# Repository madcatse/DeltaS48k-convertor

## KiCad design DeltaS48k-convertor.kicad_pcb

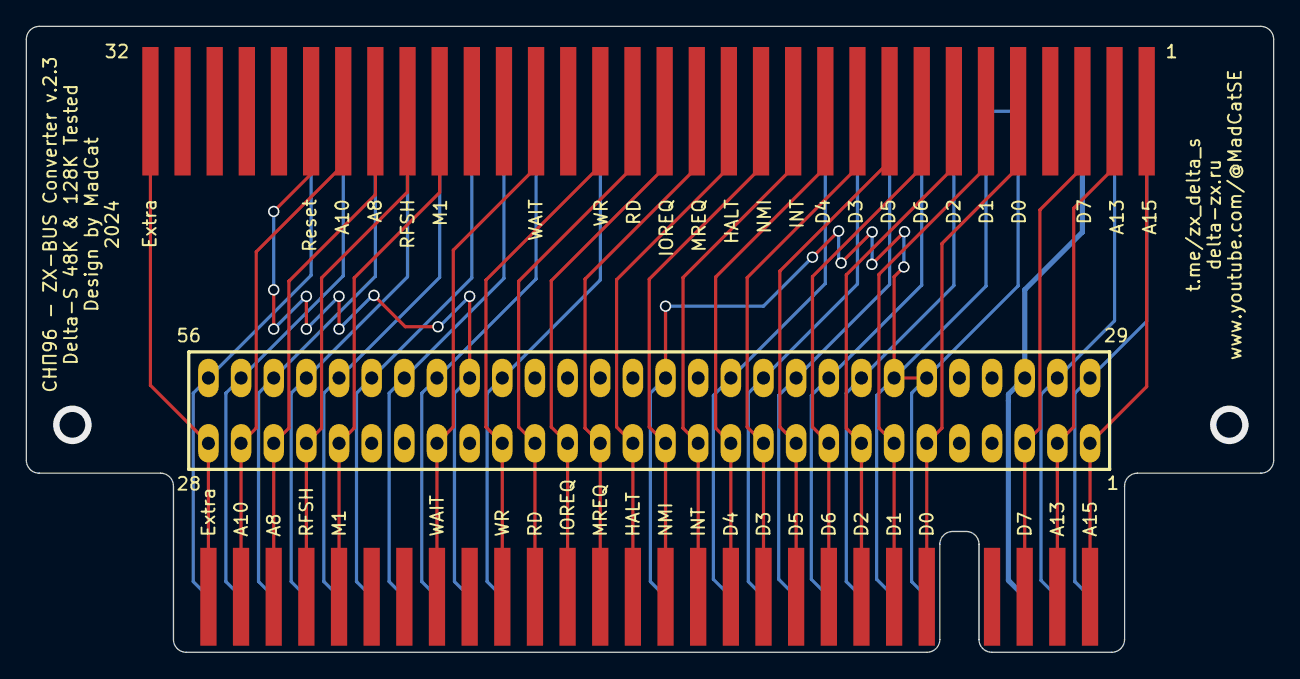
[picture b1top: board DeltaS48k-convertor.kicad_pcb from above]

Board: 2 copper layers, 97.0 x 48.7 mm, 3 parts (0 on the bottom side), 42 nets.

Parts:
J1: SNP; SNP96
J2: ZX1; ZX SPECTRUM EDGE CONNECTOR (HORIZONTAL)
SLOT: ZX1; Spectrum_edge_slot_FIXED

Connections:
A0: J1.40 (A0), J2.37 (A0), SLOT.37 (A0)
A1: J1.41 (A1), J2.38 (A1), SLOT.38 (A1)
A2: J1.42 (A2), J2.39 (A2), SLOT.39 (A2)
A3: J1.43 (A3), J2.40 (A3), SLOT.40 (A3)
A4: J1.55 (A4), J2.52 (A4), SLOT.52 (A4)
A5: J1.54 (A5), J2.51 (A5), SLOT.51 (A5)
A6: J1.53 (A6), J2.50 (A6), SLOT.50 (A6)
A7: J1.52 (A7), J2.49 (A7), SLOT.49 (A7)
A8: J1.25 (A8), J2.26 (A8), SLOT.26 (A8)
A9: J1.58 (A9), J2.55 (A9), SLOT.55 (A9)
A10: J1.26 (A10), J2.27 (A10), SLOT.27 (A10)
A11: J1.59 (A11), J2.56 (A11), SLOT.56 (A11)
A12: J1.34 (A12), J2.30 (A12), SLOT.30 (A12)
A13: J1.2 (A13), J2.2 (A13), SLOT.2 (A13)
A14: J1.33 (A14), J2.29 (A14), SLOT.29 (A14)
A15: J1.1 (A15), J2.1 (A15), SLOT.1 (A15)
BUSACK: J1.57 (ПЗШ), J2.54 (BUSACK), SLOT.54 (BUSACK)
BUSRQ: J1.50 (ЗАПРШ), J2.47 (BUSRQ), SLOT.47 (BUSRQ)
CLK: J1.39, J2.36 (CLK), SLOT.36 (CLK)
D0: J1.5 (D0), J2.6 (D0), SLOT.6 (D0)
D1: J1.6 (D1), J2.7 (D1), SLOT.7 (D1)
D2: J1.7 (D2), J2.8 (D2), SLOT.8 (D2)
D3: J1.10 (D3), J2.11 (D3), SLOT.11 (D3)
D4: J1.11 (D4), J2.12 (D4), SLOT.12 (D4)
D5: J1.9 (D5), J2.10 (D5), SLOT.10 (D5)
D6: J1.8 (D6), J2.9 (D6), SLOT.9 (D6)
D7: J1.3 (D7), J2.3 (D7), SLOT.3 (D7)
EXTRA: J1.32 (BD7), J2.28 (NC), SLOT.28 (NC)
GND: J1.37 (Общий), J1.38 (Общий), J2.34 (GND), J2.35 (GND), J2.42 (GND), SLOT.34 (GND), SLOT.35 (GND), SLOT.42 (GND)
HALT: J1.14 (СТОП), J2.15 (HALT), SLOT.15 (HALT)
INT: J1.12 (ПР), J2.13 (INT), SLOT.13 (INT)
IOREQ: J1.16 (ВУ), J2.17 (IORQ), SLOT.17 (IORQ)
M1: J1.23 (М1), J2.24 (M1), SLOT.24 (M1)
MREQ: J1.15 (ОЗУ), J2.16 (MREQ), SLOT.16 (MREQ)
NMI: J1.13 (НПР), J2.14 (NMI), SLOT.14 (NMI)
RD: J1.17 (ЧТ), J2.18 (RD), SLOT.18 (RD)
RESET: J1.27 (СБРОС), J2.48 (RESET), SLOT.48 (RESET)
RFSH: J1.24 (РГН), J2.25 (RFSH), SLOT.25 (RFSH)
ROMCS: J1.56 (БЛК_ПЗУ), J2.53 (ROMCS), SLOT.53 (ROMCS)
VCC: J1.35 ("+5"), J2.31 (+5V), SLOT.31 (+5V)
WAIT: J1.20 (ОЖИД), J2.21 (WAIT), SLOT.21 (WAIT)
WR: J1.18 (ЗП), J2.19 (WR), SLOT.19 (WR)

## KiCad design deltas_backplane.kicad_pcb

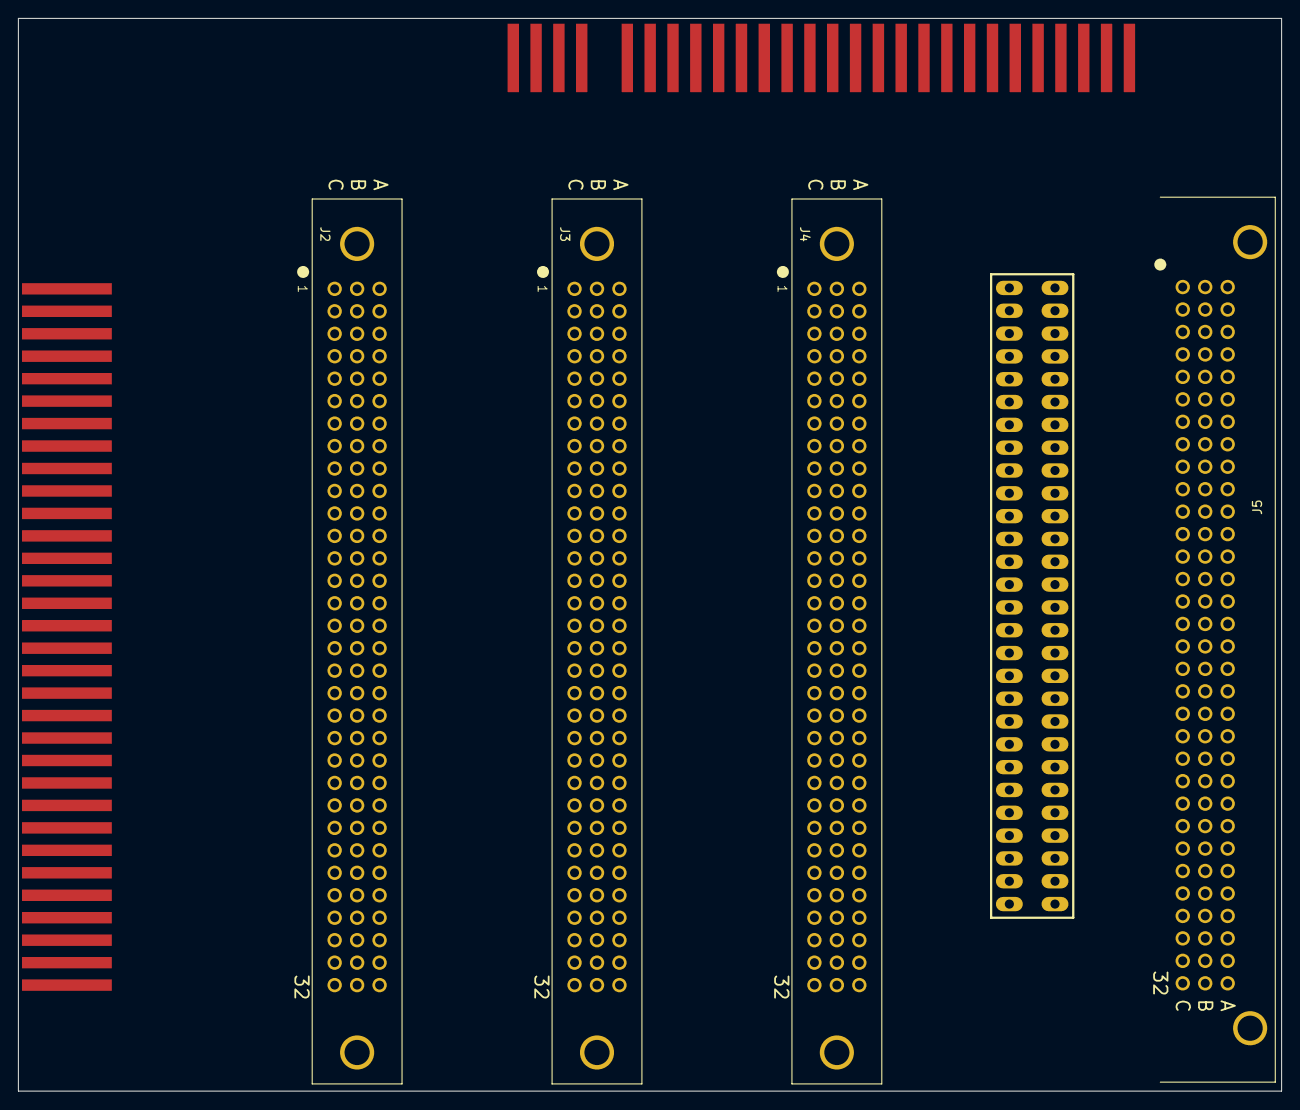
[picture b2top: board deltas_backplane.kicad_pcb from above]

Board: 2 copper layers, 140.6 x 119.4 mm, 7 parts (0 on the bottom side), 55 nets, no tracks yet.

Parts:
J1: SNP_female_straight; snp_straight
J2, J3, J4: SNP_female_straight; snp59_96_male_straight
J5: SNP_male_angle; snp59_96_female_angle_3
J6: zx_bus; ZX SPECTRUM EDGE CONNECTOR (HORIZONTAL)
J7: zx_bus; Spectrum_edge_slot_FIXED

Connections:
+5V: J1.35 ("+5"), J2.35 ("+5"), J3.35 ("+5"), J4.35 ("+5"), J5.35 ("+5"), J6.31 (+5V), J7.31 (+5V)
A0: J1.40 (A0), J2.40 (A0), J3.40 (A0), J4.40 (A0), J5.40 (A0), J6.37 (A0), J7.37 (A0)
A1: J1.41 (A1), J2.41 (A1), J3.41 (A1), J4.41 (A1), J5.41 (A1), J6.38 (A1), J7.38 (A1)
A2: J1.42 (A2), J2.42 (A2), J3.42 (A2), J4.42 (A2), J5.42 (A2), J6.39 (A2), J7.39 (A2)
A3: J1.43 (A3), J2.43 (A3), J3.43 (A3), J4.43 (A3), J5.43 (A3), J6.40 (A3), J7.40 (A3)
A4: J1.55 (A4), J2.55 (A4), J3.55 (A4), J4.55 (A4), J5.55 (A4), J6.52 (A4), J7.52 (A4)
A5: J1.54 (A5), J2.54 (A5), J3.54 (A5), J4.54 (A5), J5.54 (A5), J6.51 (A5), J7.51 (A5)
A6: J1.53 (A6), J2.53 (A6), J3.53 (A6), J4.53 (A6), J5.53 (A6), J6.50 (A6), J7.50 (A6)
A7: J1.52 (A7), J2.52 (A7), J3.52 (A7), J4.52 (A7), J5.52 (A7), J6.49 (A7), J7.49 (A7)
A8: J1.25 (A8), J2.25 (A8), J3.25 (A8), J4.25 (A8), J5.25 (A8), J6.26 (A8), J7.26 (A8)
A9: J1.58 (A9), J2.58 (A9), J3.58 (A9), J4.58 (A9), J5.58 (A9), J6.55 (A9), J7.55 (A9)
A10: J1.26 (A10), J2.26 (A10), J3.26 (A10), J4.26 (A10), J5.26 (A10), J6.27 (A10), J7.27 (A10)
A11: J1.59 (A11), J2.59 (A11), J3.59 (A11), J4.59 (A11), J5.59 (A11), J6.56 (A11), J7.56 (A11)
A12: J1.34 (A12), J2.34 (A12), J3.34 (A12), J4.34 (A12), J5.34 (A12), J6.30 (A12), J7.30 (A12)
A13: J1.2 (A13), J2.2 (A13), J3.2 (A13), J4.2 (A13), J5.2 (A13), J6.2 (A13), J7.2 (A13)
A14: J1.33 (A14), J2.33 (A14), J3.33 (A14), J4.33 (A14), J5.33 (A14), J6.29 (A14), J7.29 (A14)
A15: J1.1 (A15), J2.1 (A15), J3.1 (A15), J4.1 (A15), J5.1 (A15), J6.1 (A15), J7.1 (A15)
A19_SNP: J1.51 (BD1), J2.51 (BD1), J3.51 (BD1), J4.51 (BD1), J5.51 (BD1)
A28_SNP: J1.60 (P5), J2.60 (P5), J3.60 (P5), J4.60 (P5), J5.60 (P5)
A29_SNP: J1.61 (BD3), J2.61 (BD3), J3.61 (BD3), J4.61 (BD3), J5.61 (BD3)
A30_SNP: J1.62 (BD5), J2.62 (BD5), J3.62 (BD5), J4.62 (BD5), J5.62 (BD5)
A31_SNP: J1.63 (BD6), J2.63 (BD6), J3.63 (BD6), J4.63 (BD6), J5.63 (BD6)
B19_SNP: J1.19 (BD2), J2.19 (BD2), J3.19 (BD2), J4.19 (BD2), J5.19 (BD2)
B21_SNP: J1.21 (P1), J2.21 (P1), J3.21 (P1), J4.21 (P1), J5.21 (P1)
B22_SNP: J1.22 (P2), J2.22 (P2), J3.22 (P2), J4.22 (P2), J5.22 (P2)
B28_SNP: J1.28 (P4), J2.28 (P4), J3.28 (P4), J4.28 (P4), J5.28 (P4)
B29_SNP: J1.29 (P5), J2.29 (P5), J3.29 (P5), J4.29 (P5), J5.29 (P5)
B30_SNP: J1.30 (BD4), J2.30 (BD4), J3.30 (BD4), J4.30 (BD4), J5.30 (BD4)
B31_SNP: J1.31 (BD0), J2.31 (BD0), J3.31 (BD0), J4.31 (BD0), J5.31 (BD0)
B32_SNP: J1.32 (BD7), J2.32 (BD7), J3.32 (BD7), J4.32 (BD7), J5.32 (BD7), J6.28 (NC), J7.28 (NC)
BUSY: J1.64 (ГТ), J2.64 (ГТ), J3.64 (ГТ), J4.64 (ГТ), J5.64 (ГТ)
D0: J1.5 (D0), J2.5 (D0), J3.5 (D0), J4.5 (D0), J5.5 (D0), J6.6 (D0), J7.6 (D0)
D1: J1.6 (D1), J2.6 (D1), J3.6 (D1), J4.6 (D1), J5.6 (D1), J6.7 (D1), J7.7 (D1)
D2: J1.7 (D2), J2.7 (D2), J3.7 (D2), J4.7 (D2), J5.7 (D2), J6.8 (D2), J7.8 (D2)
D3: J1.10 (D3), J2.10 (D3), J3.10 (D3), J4.10 (D3), J5.10 (D3), J6.11 (D3), J7.11 (D3)
D4: J1.11 (D4), J2.11 (D4), J3.11 (D4), J4.11 (D4), J5.11 (D4), J6.12 (D4), J7.12 (D4)
D5: J1.9 (D5), J2.9 (D5), J3.9 (D5), J4.9 (D5), J5.9 (D5), J6.10 (D5), J7.10 (D5)
D6: J1.8 (D6), J2.8 (D6), J3.8 (D6), J4.8 (D6), J5.8 (D6), J6.9 (D6), J7.9 (D6)
D7: J1.3 (D7), J2.3 (D7), J3.3 (D7), J4.3 (D7), J5.3 (D7), J6.3 (D7), J7.3 (D7)
GND: J1.37 (Общий), J1.38 (Общий), J1.45 (Общий), J2.37 (Общий), J2.38 (Общий), J2.45 (Общий), J3.37 (Общий), J3.38 (Общий), J3.45 (Общий), J4.37 (Общий), J4.38 (Общий), J4.45 (Общий), J5.37 (Общий), J5.38 (Общий), J5.45 (Общий), J6.34 (GND), J6.35 (GND), J6.42 (GND), J7.34 (GND), J7.35 (GND), J7.42 (GND)
M1L: J1.23 (М1), J2.23 (М1), J3.23 (М1), J4.23 (М1), J5.23 (М1), J6.24 (M1), J7.24 (M1)
STROBL: J1.49 (СТР), J2.49 (СТР), J3.49 (СТР), J4.49 (СТР), J5.49 (СТР)
ВУL: J1.16 (ВУ), J2.16 (ВУ), J3.16 (ВУ), J4.16 (ВУ), J5.16 (ВУ), J6.17 (IORQ), J7.17 (IORQ)
ЗАПРШL: J1.50 (ЗАПРШ), J2.50 (ЗАПРШ), J3.50 (ЗАПРШ), J4.50 (ЗАПРШ), J5.50 (ЗАПРШ), J6.47 (BUSRQ), J7.47 (BUSRQ)
ЗПL: J1.18 (ЗП), J2.18 (ЗП), J3.18 (ЗП), J4.18 (ЗП), J5.18 (ЗП), J6.19 (WR), J7.19 (WR)
НПРL: J1.13 (НПР), J2.13 (НПР), J3.13 (НПР), J4.13 (НПР), J5.13 (НПР), J6.14 (NMI), J7.14 (NMI)
ОЖИДL: J1.20 (ОЖИД), J2.20 (ОЖИД), J3.20 (ОЖИД), J4.20 (ОЖИД), J5.20 (ОЖИД), J6.21 (WAIT), J7.21 (WAIT)
ОЗУL: J1.15 (ОЗУ), J2.15 (ОЗУ), J3.15 (ОЗУ), J4.15 (ОЗУ), J5.15 (ОЗУ), J6.16 (MREQ), J7.16 (MREQ)
ПЗШL: J1.57 (ПЗШ), J2.57 (ПЗШ), J3.57 (ПЗШ), J4.57 (ПЗШ), J5.57 (ПЗШ), J6.54 (BUSACK), J7.54 (BUSACK)
ПРL: J1.12 (ПР), J2.12 (ПР), J3.12 (ПР), J4.12 (ПР), J5.12 (ПР), J6.13 (INT), J7.13 (INT)
РГНL: J1.24 (РГН), J2.24 (РГН), J3.24 (РГН), J4.24 (РГН), J5.24 (РГН), J6.25 (RFSH), J7.25 (RFSH)
СБРОСL: J1.27 (СБРОС), J2.27 (СБРОС), J3.27 (СБРОС), J4.27 (СБРОС), J5.27 (СБРОС), J6.48 (RESET), J7.48 (RESET)
СТОПL: J1.14 (СТОП), J2.14 (СТОП), J3.14 (СТОП), J4.14 (СТОП), J5.14 (СТОП), J6.15 (HALT), J7.15 (HALT)
ЧТL: J1.17 (ЧТ), J2.17 (ЧТ), J3.17 (ЧТ), J4.17 (ЧТ), J5.17 (ЧТ), J6.18 (RD), J7.18 (RD)
ЧТПЗУL: J1.56 (БЛК_ПЗУ), J2.56 (БЛК_ПЗУ), J3.56 (БЛК_ПЗУ), J4.56 (БЛК_ПЗУ), J5.56 (БЛК_ПЗУ), J6.53 (ROMCS), J7.53 (ROMCS)

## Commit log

2023-03-19 Gerbers for ver.2.2
2023-06-05 Upload 05.06.2023
2023-06-07 Add 3d model
2023-09-30 Initial
2023-10-01 Cleanup
2023-10-01 Version 0.1
2023-10-01 Service
2023-10-01 Small update
2023-10-03 Backup reverting
2023-10-11 Added gerber files
2023-10-20 Update fp-info-cache
2024-02-01 First version fix
2024-02-04 Fixed ZX Bus conector width
